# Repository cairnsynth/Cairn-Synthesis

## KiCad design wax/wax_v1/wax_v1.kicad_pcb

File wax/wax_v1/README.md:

# Wax V1
Wax V1 is a passive multiple module (V2 for buffered mults comming?). It functions as a 1x6 or 2x3 multiple, with the inputs normalised together.

## Operation
- The 2 inputs are marked with the solid polys. They are normalised together, meaning if a single input is used, the signal will be propagated to all 6 outputs.
- The outputs are marked with the hollow polys.
- The passive nature of `Wax V1` means that it is best used for triggers/gates and CV signals where accurate voltage tracking is not required.
- For driving several oscillators, where accurate 1v/Oct tracking is important, it would be best to use a buffered mult.

## Repo Overview
- `wax_v1_FP` : KiCAD project files for the module front panel
- `wax_v1_FP_gerber` : fabrication files for the front panel PCB (JLCPCB spec)
- `wax_v1_FP_graphics` : SVG graphics used in the development of the front panel PCB
- `wax_v1_PCB` : KICAD project files for the main PCB
- `wax_v1_PCB_gerber` : fabrication files for the main PCB (JLCPCB spec)

## Build Notes
- The main PCB can be manufactured as a 2 layer PCB, using default settings on JLCPCB
- The front panel can also use mostly default settings too.
	+ It was designed with black solder resist in mind
	+ ENIG surface finish may give the best results/longevity of the metal designs
- Ground pads are shared between pairs of jack sockets
- Knurled nuts are probably the best option aesthetically
	+ I didn't consider the radius of the nut when designing the front panel graphics
	+ Befaco knurled nuts look good, in a combination of black and yellow, but there may be some overlap of the graphics due to the larger diameter when compared to a standard knurled nut

## BOM
| Part | Qty |
|------|-----|
|wax_v1_PCB|1|
|wax_v1_FP |1|
|Thonkiconn mono jack|8|
|Knurled m6 nut|8|

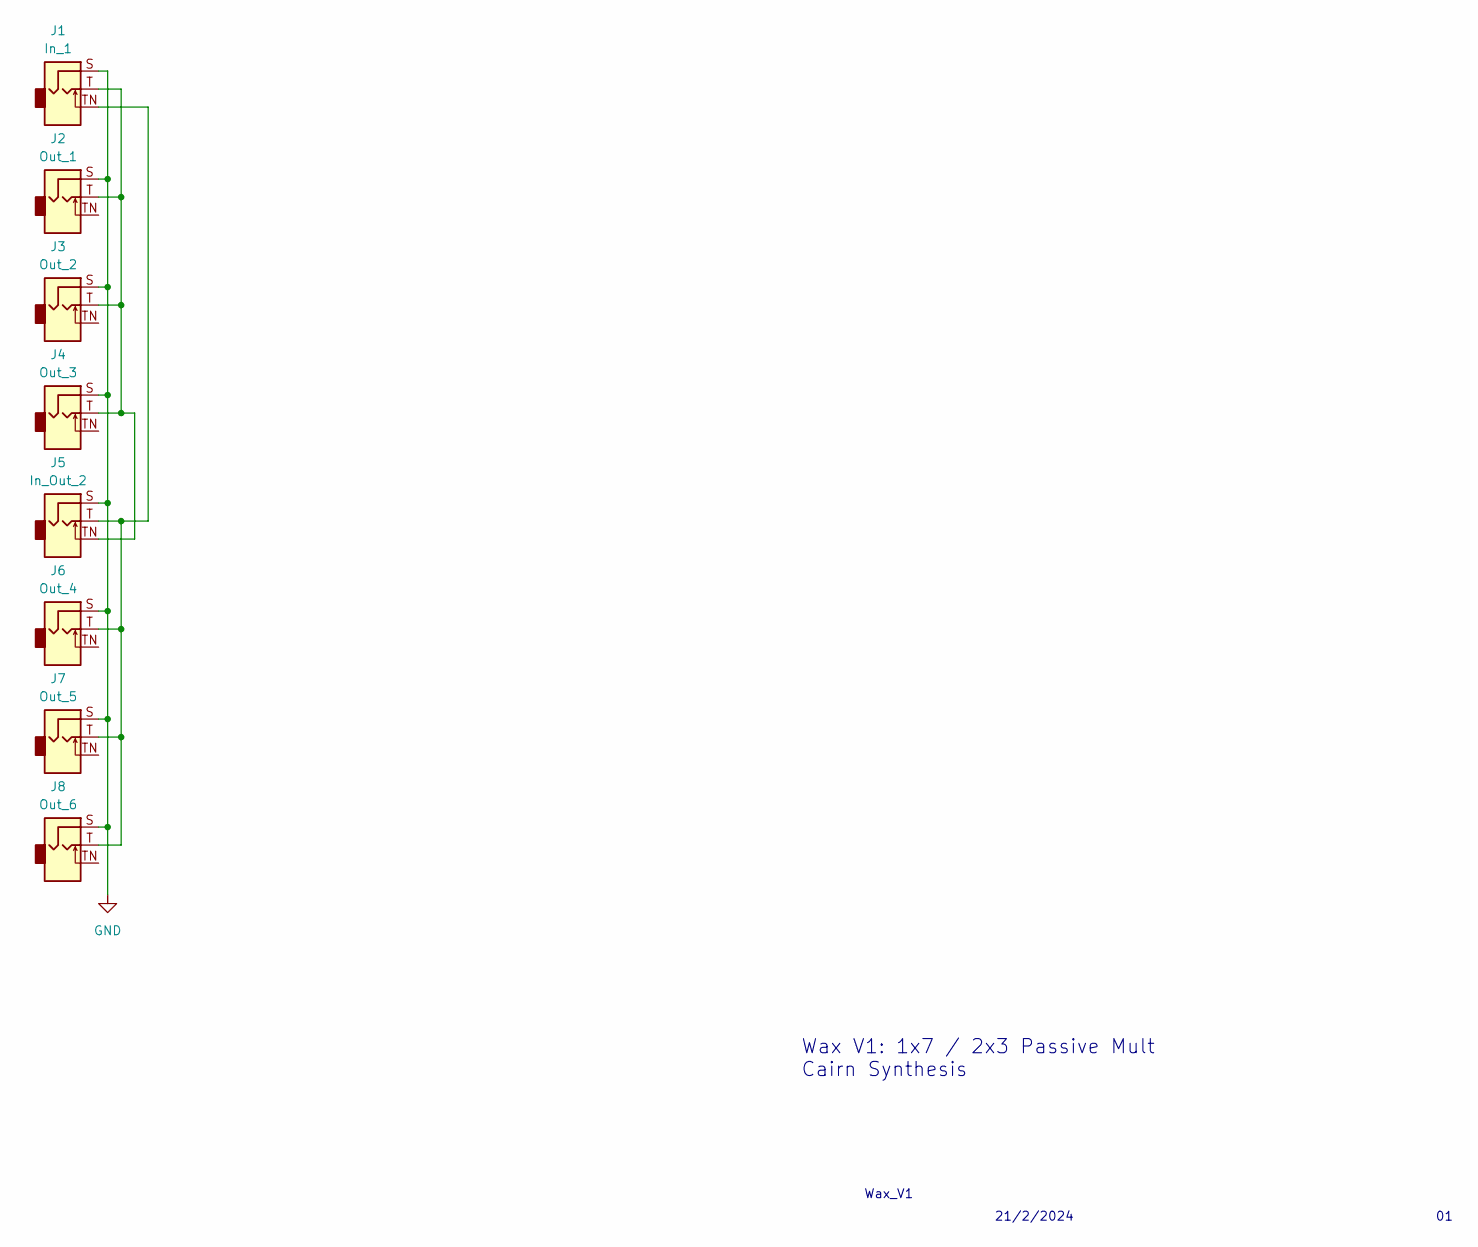
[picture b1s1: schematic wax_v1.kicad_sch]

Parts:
J1: In_1; Jack_3.5mm_QingPu_WQP-PJ398SM_Vertical_CircularHoles
J2: Out_1; Jack_3.5mm_QingPu_WQP-PJ398SM_Vertical_CircularHoles
J3: Out_2; Jack_3.5mm_QingPu_WQP-PJ398SM_Vertical_CircularHoles
J4: Out_3; Jack_3.5mm_QingPu_WQP-PJ398SM_Vertical_CircularHoles
J5: In_Out_2; Jack_3.5mm_QingPu_WQP-PJ398SM_Vertical_CircularHoles
J6: Out_4; Jack_3.5mm_QingPu_WQP-PJ398SM_Vertical_CircularHoles
J7: Out_5; Jack_3.5mm_QingPu_WQP-PJ398SM_Vertical_CircularHoles
J8: Out_6; Jack_3.5mm_QingPu_WQP-PJ398SM_Vertical_CircularHoles

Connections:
GND: J1.S, J2.S, J3.S, J4.S, J5.S, J6.S, J7.S, J8.S
unnamed: J1.T, J2.T, J3.T, J4.T, J5.TN
unnamed: J1.TN, J5.T, J6.T, J7.T, J8.T

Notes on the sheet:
Wax V1: 1x7 / 2x3 Passive Mult Cairn Synthesis
Wax_V1
21/2/2024

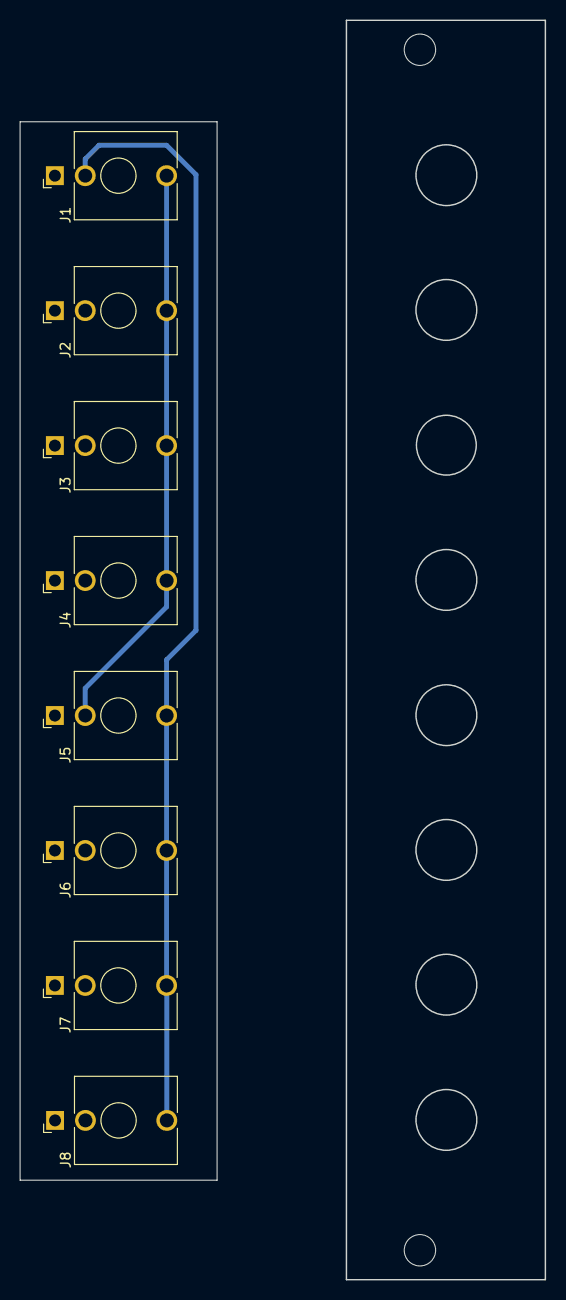
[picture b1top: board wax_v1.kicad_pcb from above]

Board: 2 copper layers, 20.1 x 108.0 mm, 8 parts (0 on the bottom side), 3 nets.

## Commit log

2024-01-22 Repo init, bone charm started
2024-01-22 Bone Charm project setup
2024-02-02 IO page added
2024-02-21 Wax V1 schematic done
2024-02-21 Wax V1 pcb main layout done, front pannel started
2024-09-22 Wax V1 FP, PCB, gerbers added
2024-09-22 Wax V1 README added
